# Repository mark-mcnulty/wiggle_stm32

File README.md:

# STM32_MOD_2

Firmware for a small STM32F1-based audio board: either a LUT-driven oscillator into the onboard DAC, or a short effects chain on whatever comes in on the ADC. The Cube/HAL setup is real; mixer, filter, ADSR, and sampler are mostly placeholders for now (see [Code layout](#code-layout)).

**MCU:** STM32F103RCT6  
**IDE:** STM32CubeIDE (GCC).

## Requirements

- [STM32CubeIDE](https://www.st.com/en/development-tools/stm32cubeide.html) (or IAR + pack for F1)
- ST firmware package **STM32Cube FW_F1 V1.8.6** (matches [`STM32_MOD_2.ioc`](STM32_MOD_2.ioc))

## Build and flash

1. Open [`STM32_MOD_2.ioc`](STM32_MOD_2.ioc) or import the project from this repo in CubeIDE.
2. Build the **Debug** configuration (output under `Debug/`).
3. Flash/debug with your ST-Link (or whatever probe you use in the launch config).

Regenerating code from the `.ioc` is fine; user sections in `main.c` and friends are preserved by Cube’s `USER CODE` blocks.

## Audio modes

Flip these in [`Core/Src/main.c`](Core/Src/main.c) before you build:

- `ACTIVE_AUDIO_MODE` — `SYNTH` or `EFFECTS` (passed into `init_stm32()`).
- `ACTIVE_EFFECT_MODE` — `EFFECT_BYPASS`, `EFFECT_MOVING_AVG`, or `EFFECT_BIT_CRUSHER` ([`Core/Inc/effects.h`](Core/Inc/effects.h)).
- `ACTIVE_MOVING_AVG_TAPS` — tap count for the moving average (capped in [`effects.c`](Core/Src/effects.c)).

**SYNTH:** TIM8 triggers DAC channel 2 via DMA. Half- and full-transfer callbacks call `render_audio_block()`, which fills the DAC buffer from the oscillator ([`Core/Src/stm32_synth.c`](Core/Src/stm32_synth.c), [`Core/Src/oscillator.c`](Core/Src/oscillator.c)). Waveforms are sine, square, triangle, saw, or noise ([`Core/Inc/oscillator.h`](Core/Inc/oscillator.h)). Right now the main loop runs `marry_had_a_little_lamb()` as a demo when in this mode; other tests (UART, frequency sweep, seven-seg) are commented out in the same file.

**EFFECTS:** ADC1 is also triggered off TIM8 TRGO, with DMA into `audio_buffer_adc`. ADC callbacks copy each half into `audio_buffer_sig_path`. DAC callbacks wait until the matching `adc_half_ready[]` flag is set, then run `effects_process_sample()` so output stays aligned with fresh input. Underrun/overrun counters on `struct synth` are there for debugging.

**Sample rate:** System clock is 24 MHz (HSI + PLL in `SystemClock_Config`). TIM8 is set in the IOC to prescaler 3 and period 124, which works out to about **48 kHz** for the DAC/ADC trigger rate. Audio buffers are **256** samples (`AUDIO_BUFFER_SIZE` in [`Core/Inc/stm32_synth.h`](Core/Inc/stm32_synth.h)).

## Front-panel I/O

Pin names live in [`Core/Inc/main.h`](Core/Inc/main.h): two buttons, a pot, an LED, SPI1 to a shift-register style display, plus digit select lines for a **two-digit seven-segment** display. [`Core/Src/seven_seg.c`](Core/Src/seven_seg.c) is refreshed from `HAL_TIM_PeriodElapsedCallback()` on TIM2 in `main.c`.

## Code layout

| Area | Files |
|------|--------|
| Entry, Cube init, DAC/ADC callbacks | [`Core/Src/main.c`](Core/Src/main.c) |
| Mode init, `render_audio_block`, ADC staging | [`Core/Src/stm32_synth.c`](Core/Src/stm32_synth.c), [`Core/Inc/stm32_synth.h`](Core/Inc/stm32_synth.h) |
| Oscillator / LUT | [`Core/Src/oscillator.c`](Core/Src/oscillator.c), [`Core/Inc/oscillator.h`](Core/Inc/oscillator.h) |
| Effects | [`Core/Src/effects.c`](Core/Src/effects.c), [`Core/Inc/effects.h`](Core/Inc/effects.h) |
| Note frequencies | [`Core/Inc/notes.h`](Core/Inc/notes.h) |
| Seven-segment + SPI | [`Core/Src/seven_seg.c`](Core/Src/seven_seg.c), [`Core/Inc/seven_seg.h`](Core/Inc/seven_seg.h) |

**Not wired into the synth audio path yet:** `struct synth` already holds mixer, filter, and ADSR, and [`mixer.c`](Core/Src/mixer.c) implements a simple average of sources, but `render_audio_block()` only comments those stages—no calls. [`filter.c`](Core/Src/filter.c), [`adsr.c`](Core/Src/adsr.c), and [`sampler.c`](Core/Src/sampler.c) are empty or stub implementations.

## Hardware and diagrams

KiCad lives under [`Hardware/`](Hardware/). The project file is [`Hardware/STM_Module.kicad_pro`](Hardware/STM_Module.kicad_pro); schematics include e.g. [`Hardware/STM32.kicad_sch`](Hardware/STM32.kicad_sch) and [`Hardware/power.kicad_sch`](Hardware/power.kicad_sch).

Block diagrams in the repo root: [`signal_path_diagram.drawio`](signal_path_diagram.drawio), [`stm32_structure.drawio`](stm32_structure.drawio).

## License

ST’s HAL/CMSIS drop in with their usual `LICENSE.txt` under `Drivers/`—nothing special added here.

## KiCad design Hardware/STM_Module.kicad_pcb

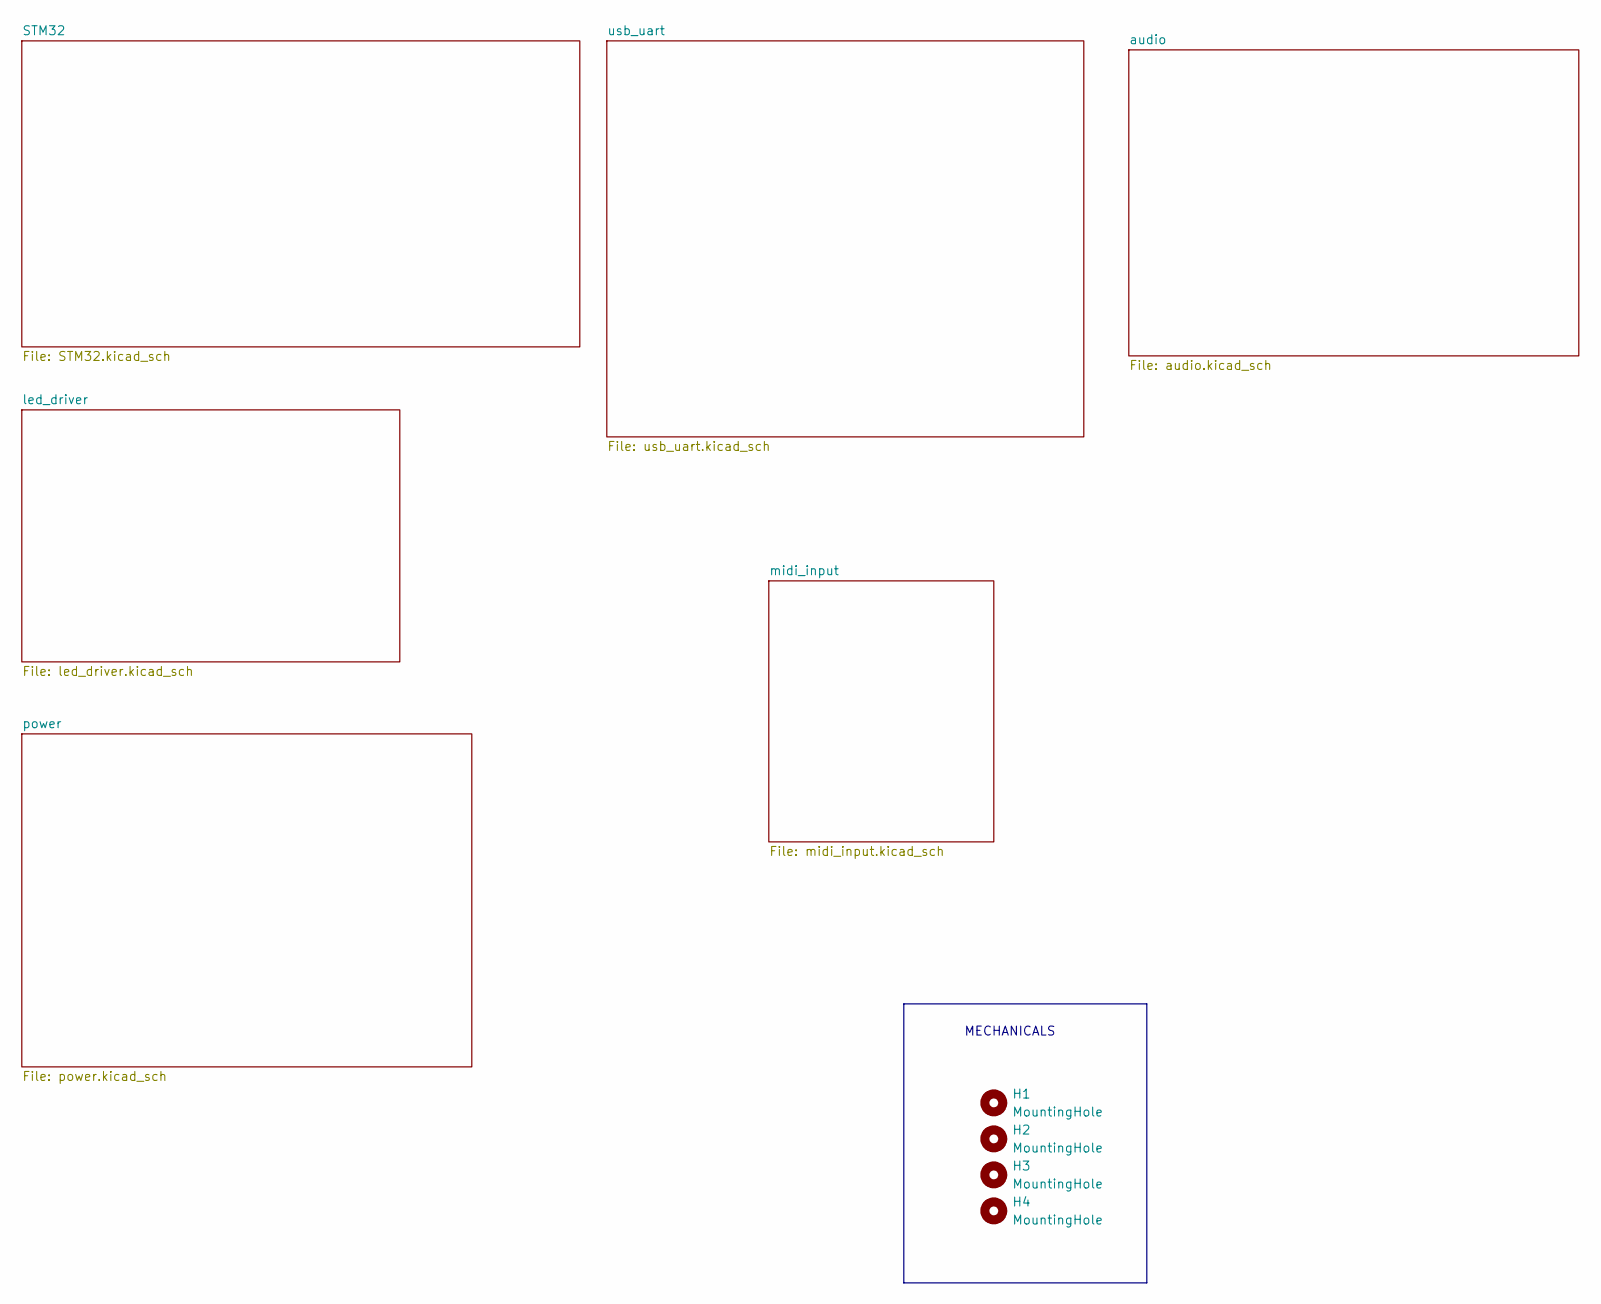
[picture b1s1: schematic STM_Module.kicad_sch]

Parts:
H1, H2, H3, H4: MountingHole; MountingHole_2.2mm_M2

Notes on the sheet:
MECHANICALS

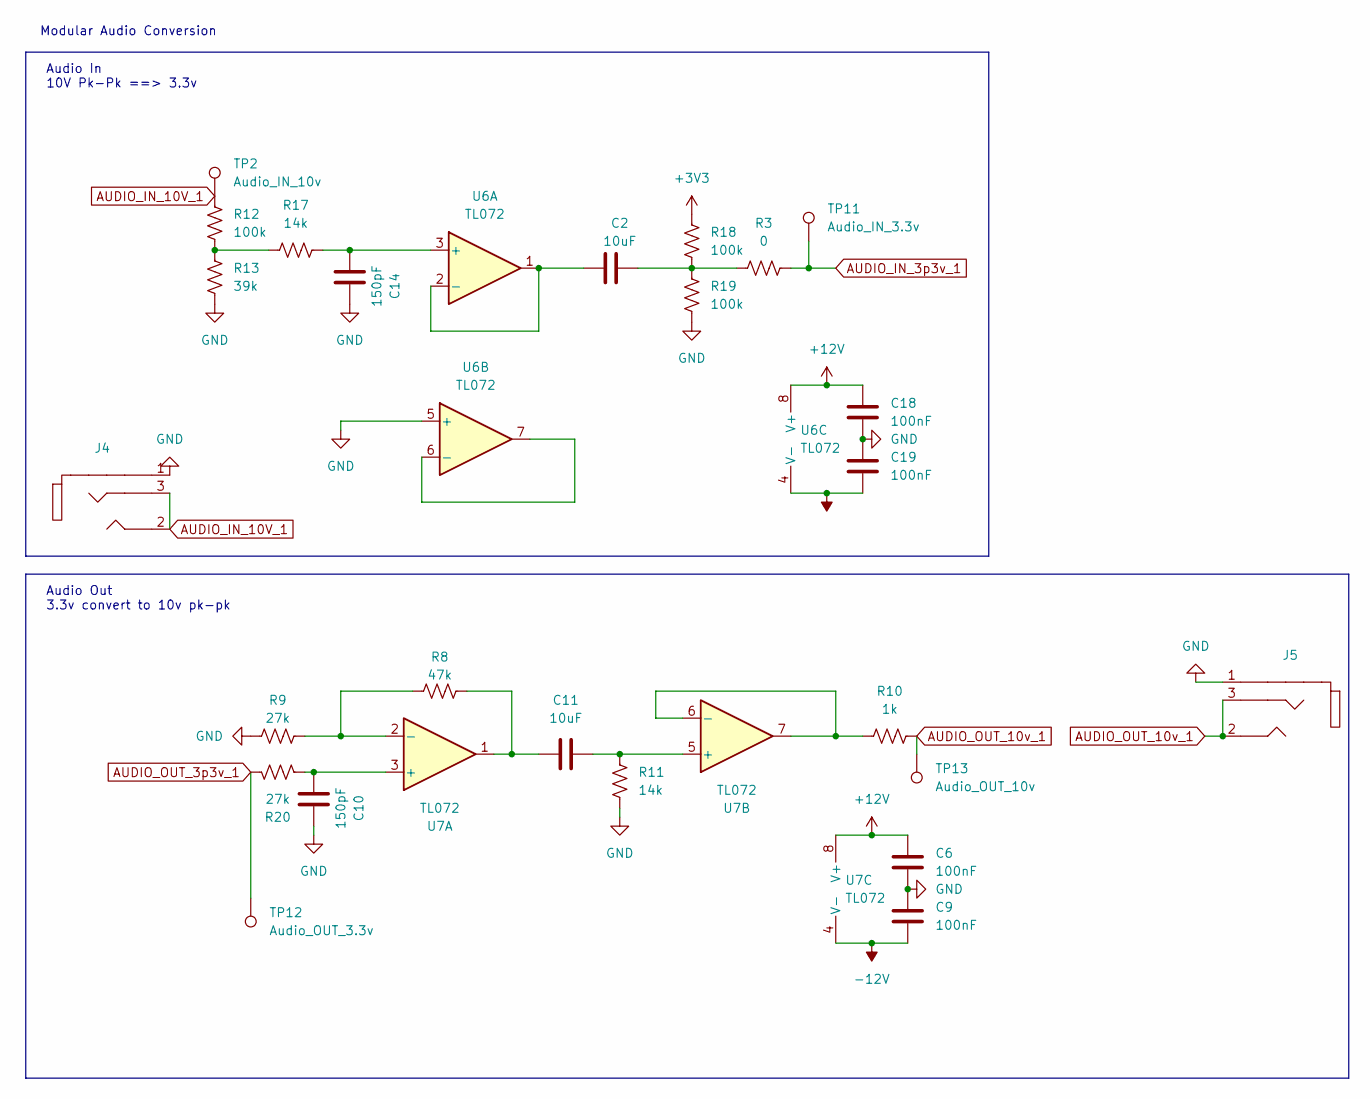
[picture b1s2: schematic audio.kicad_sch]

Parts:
C2, C11: 10uF; C_1206_3216Metric
C6, C9, C18, C19: 100nF; C_1206_3216Metric
C10, C14: 150pF; C_1206_3216Metric
J4, J5: aux
R3: 0; R_1206_3216Metric
R8: 47k; R_1206_3216Metric
R9, R20: 27k; R_1206_3216Metric
R10: 1k; R_1206_3216Metric
R11, R17: 14k; R_1206_3216Metric
R12, R18, R19: 100k; R_1206_3216Metric
R13: 39k; R_1206_3216Metric
TP2: Audio_IN_10v; PinHeader_1x01_P2.54mm_Vertical
TP11: Audio_IN_3.3v; PinHeader_1x01_P2.54mm_Vertical
TP12: Audio_OUT_3.3v; PinHeader_1x01_P2.54mm_Vertical
TP13: Audio_OUT_10v; PinHeader_1x01_P2.54mm_Vertical
U6, U7: TL072; TL072_SOIC-8

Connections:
+3V3: R18.1; also elsewhere on the board
+12V: C6.2, C18.2, U6.8 (V+), U7.8 (V+); also elsewhere on the board
-12V: C9.1, C19.1, U6.4 (V-), U7.4 (V-); also elsewhere on the board
AUDIO_IN_3p3v_1: R3.2, TP11.1; also elsewhere on the board
AUDIO_IN_10V_1: J4.2, J4.3, R12.1, TP2.1
AUDIO_OUT_3p3v_1: R20.1, TP12.1; also elsewhere on the board
AUDIO_OUT_10v_1: J5.2, J5.3, R10.2, TP13.1
GND: C6.1, C9.2, C10.1, C14.1, C18.1, C19.2, J4.1, J5.1, R9.1, R11.1, R13.2, R19.2, U6.5 (+); also elsewhere on the board
unnamed: C2.1, R3.1, R18.2, R19.1
unnamed: C11.2, R8.2, U7.1
unnamed: R12.2, R13.1, R17.1
unnamed: C14.2, R17.2, U6.3 (+)
unnamed: C2.2, U6.1, U6.2 (-)
unnamed: U6.6 (-), U6.7
unnamed: C10.2, R20.2, U7.3 (+)
unnamed: R8.1, R9.2, U7.2 (-)
unnamed: C11.1, R11.2, U7.5 (+)
unnamed: R10.1, U7.6 (-), U7.7

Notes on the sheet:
Audio Out 3.3v convert to 10v pk-pk
Audio In 10V Pk-Pk ==> 3.3v
Modular Audio Conversion

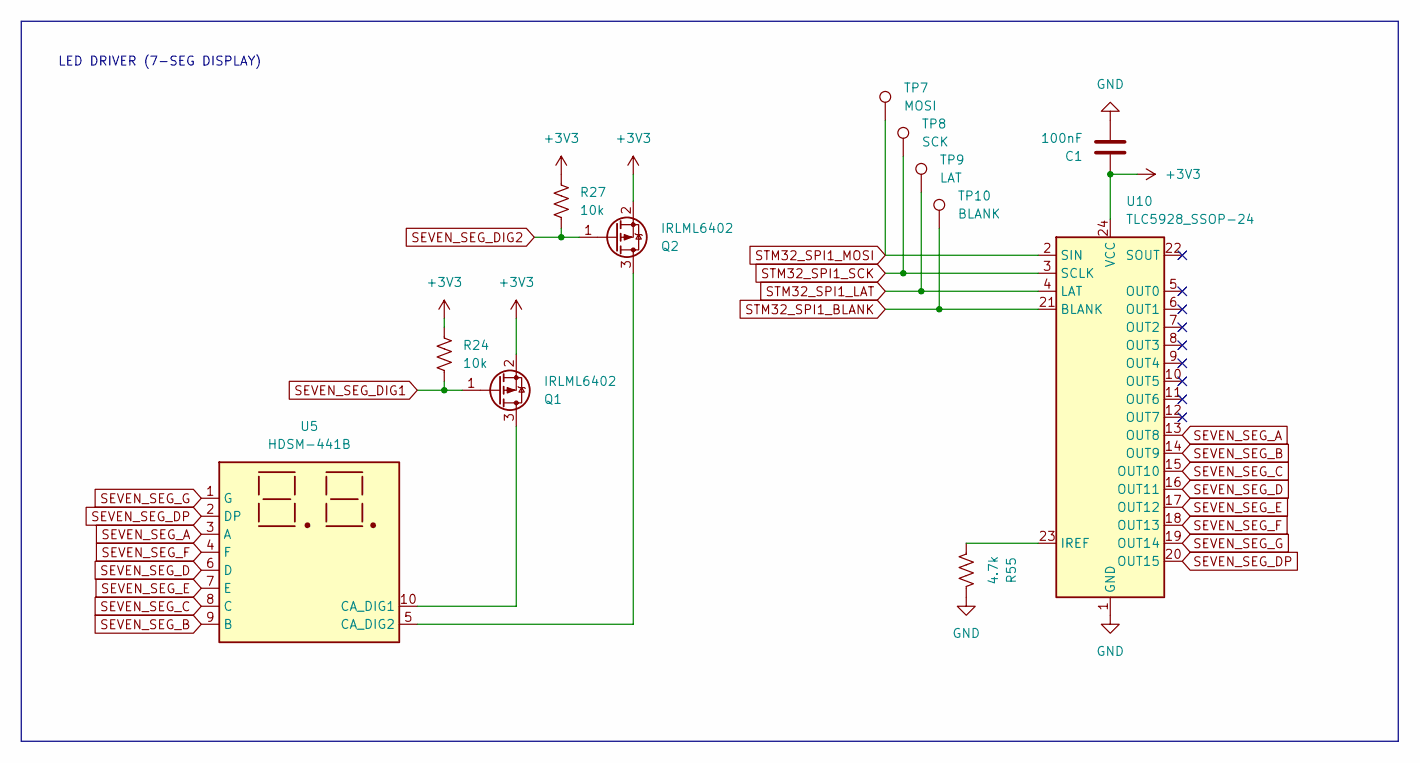
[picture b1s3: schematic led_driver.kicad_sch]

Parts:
C1: 100nF; C_1206_3216Metric
Q1, Q2: IRLML6402; SOT-23
R24, R27: 10k; R_1206_3216Metric
R55: 4.7k; R_1206_3216Metric
TP7: MOSI; PinHeader_1x01_P2.54mm_Vertical
TP8: SCK; PinHeader_1x01_P2.54mm_Vertical
TP9: LAT; PinHeader_1x01_P2.54mm_Vertical
TP10: BLANK; PinHeader_1x01_P2.54mm_Vertical
U5: HDSM-441B; 2x7 SEG LCSC C193139
U10: TLC5928_SSOP-24

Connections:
+3V3: C1.1, Q1.2 (S), Q2.2 (S), R24.1, R27.1, U10.24 (VCC); also elsewhere on the board
GND: C1.2, R55.1, U10.1 (GND); also elsewhere on the board
unnamed: Q1.3 (D), U5.10 (CA_DIG1)
unnamed: Q2.3 (D), U5.5 (CA_DIG2)
unnamed: R55.2, U10.23 (IREF)
SEVEN_SEG_A: U5.3 (A), U10.13 (OUT8)
SEVEN_SEG_B: U5.9 (B), U10.14 (OUT9)
SEVEN_SEG_C: U5.8 (C), U10.15 (OUT10)
SEVEN_SEG_D: U5.6 (D), U10.16 (OUT11)
SEVEN_SEG_DIG1: Q1.1 (G), R24.2; also elsewhere on the board
SEVEN_SEG_DIG2: Q2.1 (G), R27.2; also elsewhere on the board
SEVEN_SEG_DP: U5.2 (DP), U10.20 (OUT15)
SEVEN_SEG_E: U5.7 (E), U10.17 (OUT12)
SEVEN_SEG_F: U5.4 (F), U10.18 (OUT13)
SEVEN_SEG_G: U5.1 (G), U10.19 (OUT14)
STM32_SPI1_BLANK: TP10.1, U10.21 (BLANK); also elsewhere on the board
STM32_SPI1_LAT: TP9.1, U10.4 (LAT); also elsewhere on the board
STM32_SPI1_MOSI: TP7.1, U10.2 (SIN); also elsewhere on the board
STM32_SPI1_SCK: TP8.1, U10.3 (SCLK); also elsewhere on the board

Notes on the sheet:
LED DRIVER (7-SEG DISPLAY)

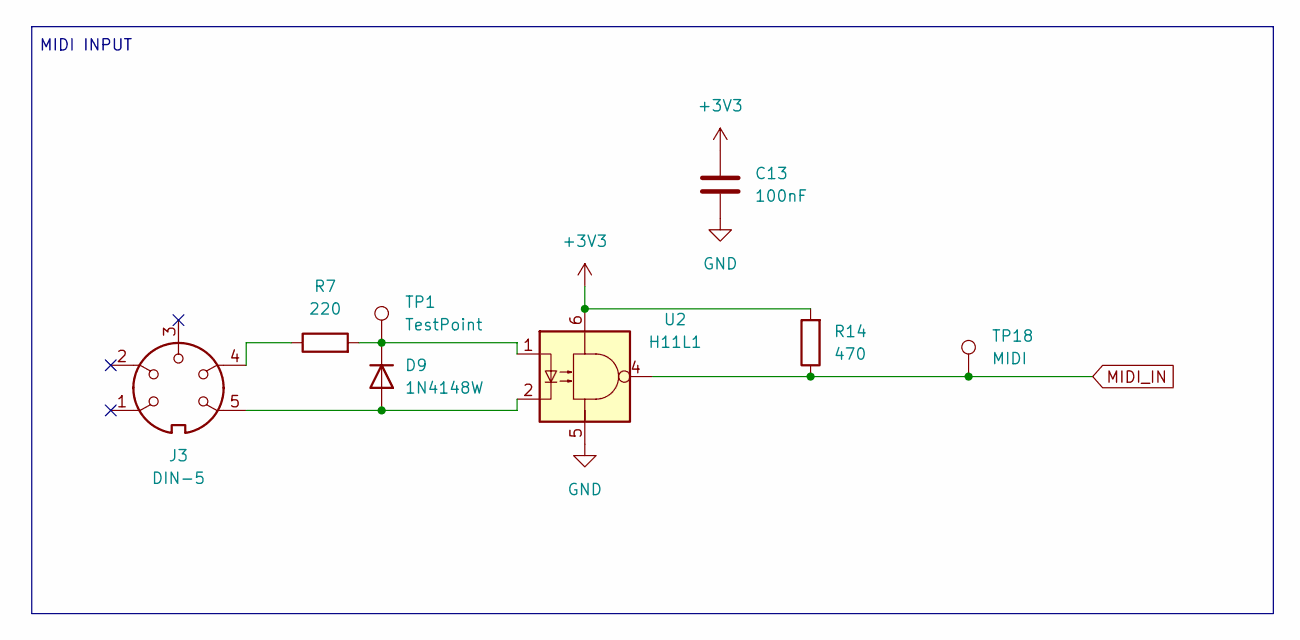
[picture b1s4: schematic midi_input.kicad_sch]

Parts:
C13: 100nF; C_1206_3216Metric
D9: 1N4148W; D_SOD-123
J3: DIN-5; Din5
R7: 220; R_1206_3216Metric
R14: 470; R_1206_3216Metric
TP1: TestPoint; PinHeader_1x01_P2.54mm_Vertical
TP18: MIDI; PinHeader_1x01_P2.54mm_Vertical
U2: H11L1; H11L1_SMD

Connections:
+3V3: C13.1, R14.2, U2.6; also elsewhere on the board
GND: C13.2, U2.5; also elsewhere on the board
MIDI_IN: R14.1, TP18.1, U2.4; also elsewhere on the board
unnamed: D9.2 (A), J3.5, U2.2
unnamed: D9.1 (K), R7.2, TP1.1, U2.1
unnamed: J3.4, R7.1

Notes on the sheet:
MIDI INPUT

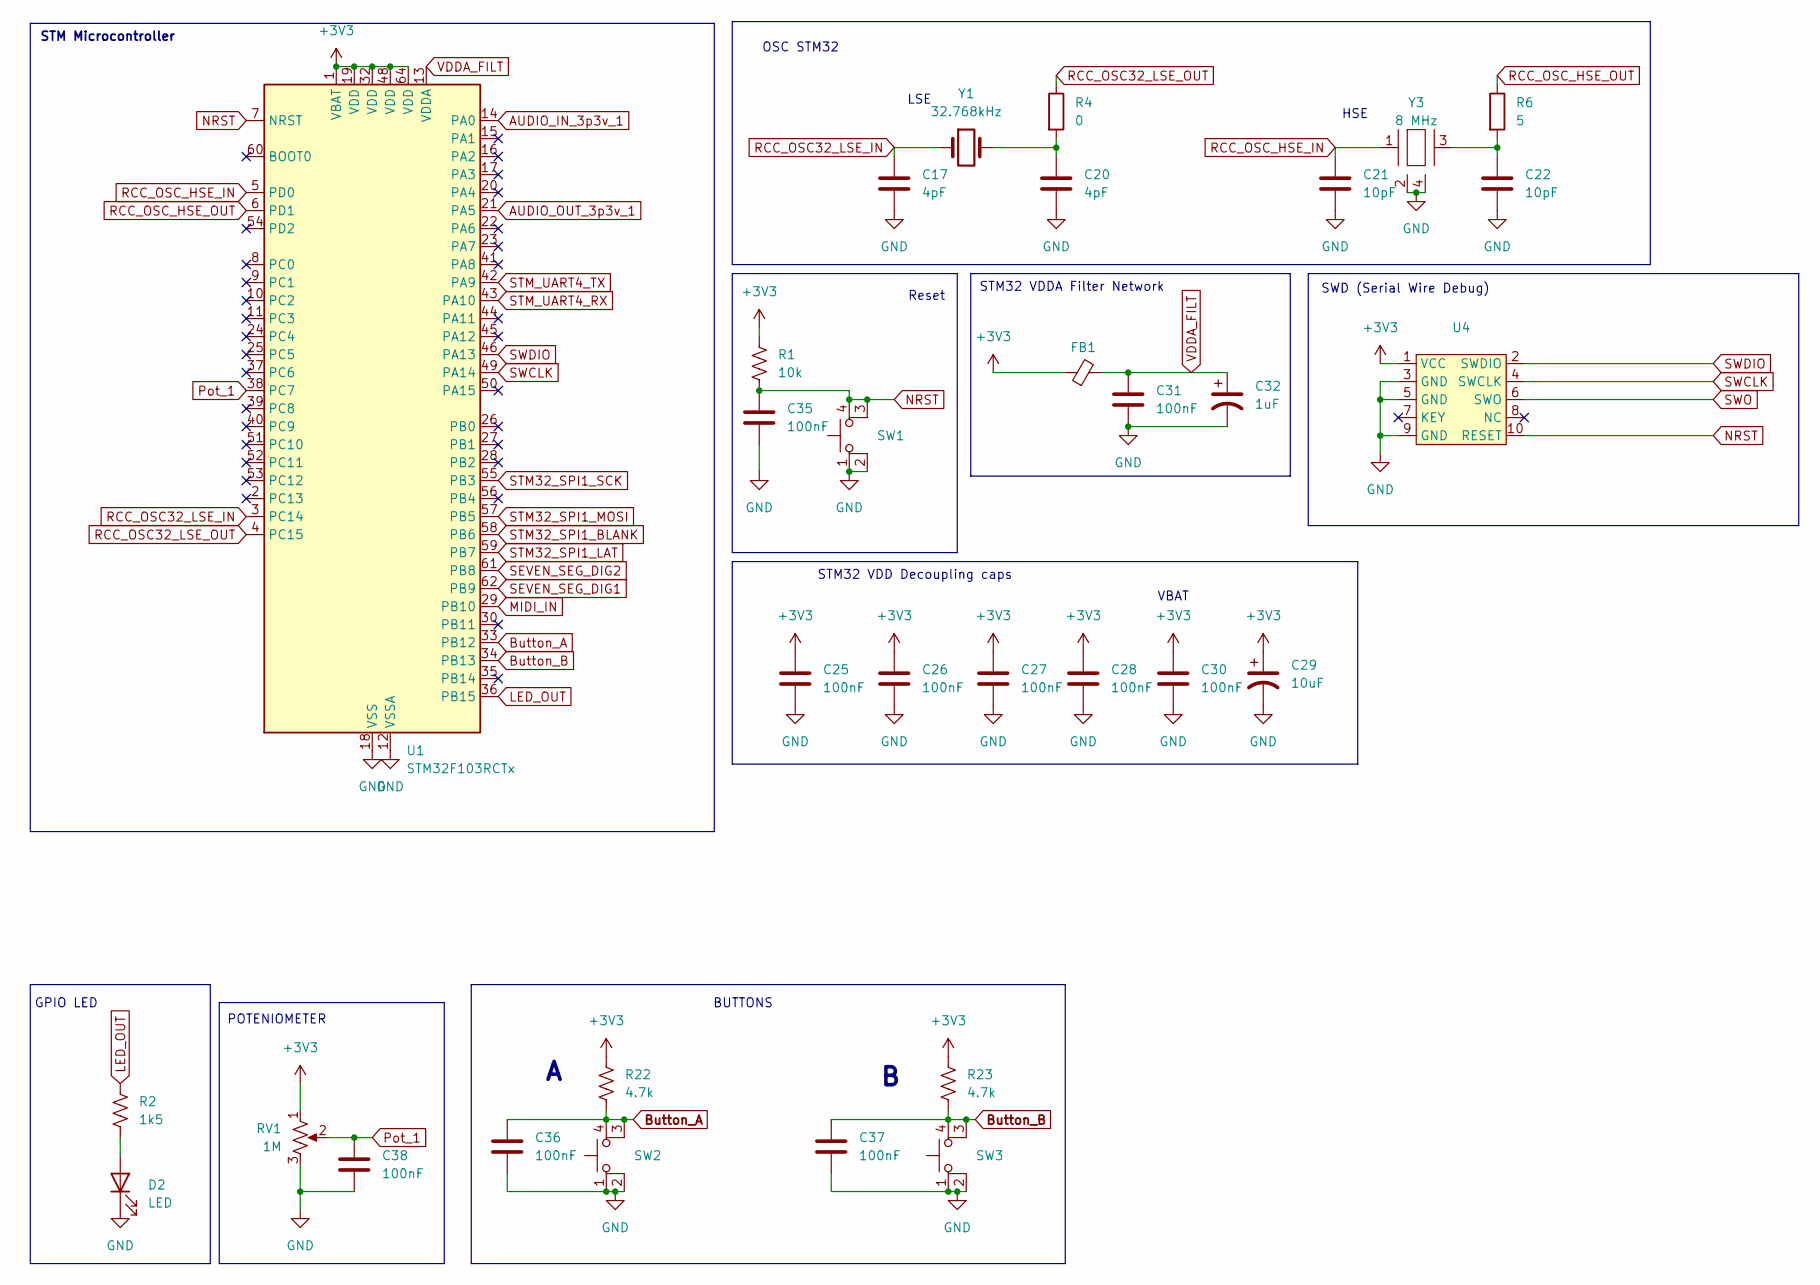
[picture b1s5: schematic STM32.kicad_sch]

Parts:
C17, C20: 4pF; C_0603_1608Metric
C21, C22: 10pF; C_0603_1608Metric
C25, C26, C27, C28, C30, C31, C35, C36, C37, C38: 100nF; C_1206_3216Metric
C29: 10uF; CP_Elec_4x5.4
C32: 1uF; CP_Elec_4x5.4
D2: LED; LED_1206_3216Metric
FB1: FerriteBead_Small; R_1206_3216Metric
R1: 10k; R_1206_3216Metric
R2: 1k5; R_1206_3216Metric
R4: 0; R_1206_3216Metric
R6: 5; R_1206_3216Metric
R22, R23: 4.7k; R_1206_3216Metric
RV1: 1M; POT_mogaopi
SW1, SW2, SW3: SW_MEC_5E; Button PN C381039
U1: STM32F103RCTx; LQFP-64_10x10mm_P0.5mm
U4: PinHeader_2x05_P2.54mm_Vertical
Y1: 32.768kHz; Crystal_SMD_2012-2Pin_2.0x1.2mm
Y3: 8 MHz; 12MHz Surface Mount Crystal 12pF ±10ppm ±20ppm SMD3225-4P C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

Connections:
+3V3: C25.2, C26.2, C27.2, C28.2, C29.1, C30.2, FB1.1, R1.2, R22.1, R23.1, RV1.1, U1.1 (VBAT), U1.19 (VDD), U1.32 (VDD), U1.48 (VDD), U1.64 (VDD), U4.1 (VCC); also elsewhere on the board
AUDIO_IN_3p3v_1: U1.14 (PA0); also elsewhere on the board
AUDIO_OUT_3p3v_1: U1.21 (PA5); also elsewhere on the board
Button_A: C36.2, R22.2, SW2.3 (K), SW2.4 (A), U1.33 (PB12)
Button_B: C37.2, R23.2, SW3.3 (K), SW3.4 (A), U1.34 (PB13)
GND: C17.1, C20.1, C21.1, C22.1, C25.1, C26.1, C27.1, C28.1, C29.2, C30.1, C31.1, C32.2, C35.1, C36.1, C37.1, C38.1, D2.1 (K), RV1.3, SW1.1, SW1.2, SW2.1, SW2.2, SW3.1, SW3.2, U1.12 (VSSA), U1.18 (VSS), U1.31 (VSS), U1.47 (VSS), U1.63 (VSS), U4.3 (GND), U4.5 (GND), U4.9 (GND), Y3.2, Y3.4; also elsewhere on the board
LED_OUT: R2.1, U1.36 (PB15)
MIDI_IN: U1.29 (PB10); also elsewhere on the board
NRST: C35.2, R1.1, SW1.3 (K), SW1.4 (A), U1.7 (NRST), U4.10 (RESET)
unnamed: C20.2, R4.2, Y1.2
unnamed: C22.2, R6.2, Y3.3
unnamed: D2.2 (A), R2.2
Pot_1: C38.2, RV1.2, U1.38 (PC7)
RCC_OSC32_LSE_IN: C17.2, U1.3 (PC14), Y1.1
RCC_OSC32_LSE_OUT: R4.1, U1.4 (PC15)
RCC_OSC_HSE_IN: C21.2, U1.5 (PD0), Y3.1
RCC_OSC_HSE_OUT: R6.1, U1.6 (PD1)
SEVEN_SEG_DIG1: U1.62 (PB9); also elsewhere on the board
SEVEN_SEG_DIG2: U1.61 (PB8); also elsewhere on the board
STM32_SPI1_BLANK: U1.58 (PB6); also elsewhere on the board
STM32_SPI1_LAT: U1.59 (PB7); also elsewhere on the board
STM32_SPI1_MOSI: U1.57 (PB5); also elsewhere on the board
STM32_SPI1_SCK: U1.55 (PB3); also elsewhere on the board
STM_UART4_RX: U1.43 (PA10); also elsewhere on the board
STM_UART4_TX: U1.42 (PA9); also elsewhere on the board
SWCLK: U1.49 (PA14), U4.4 (SWCLK)
SWDIO: U1.46 (PA13), U4.2 (SWDIO)
SWO: U4.6 (SWO)
VDDA_FILT: C31.2, C32.1, FB1.2, U1.13 (VDDA)

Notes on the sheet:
STM Microcontroller
LSE
VBAT
GPIO LED
STM32 VDDA Filter Network
OSC STM32
BUTTONS
STM32 VDD Decoupling caps
Reset
POTENIOMETER
SWD (Serial Wire Debug)
HSE

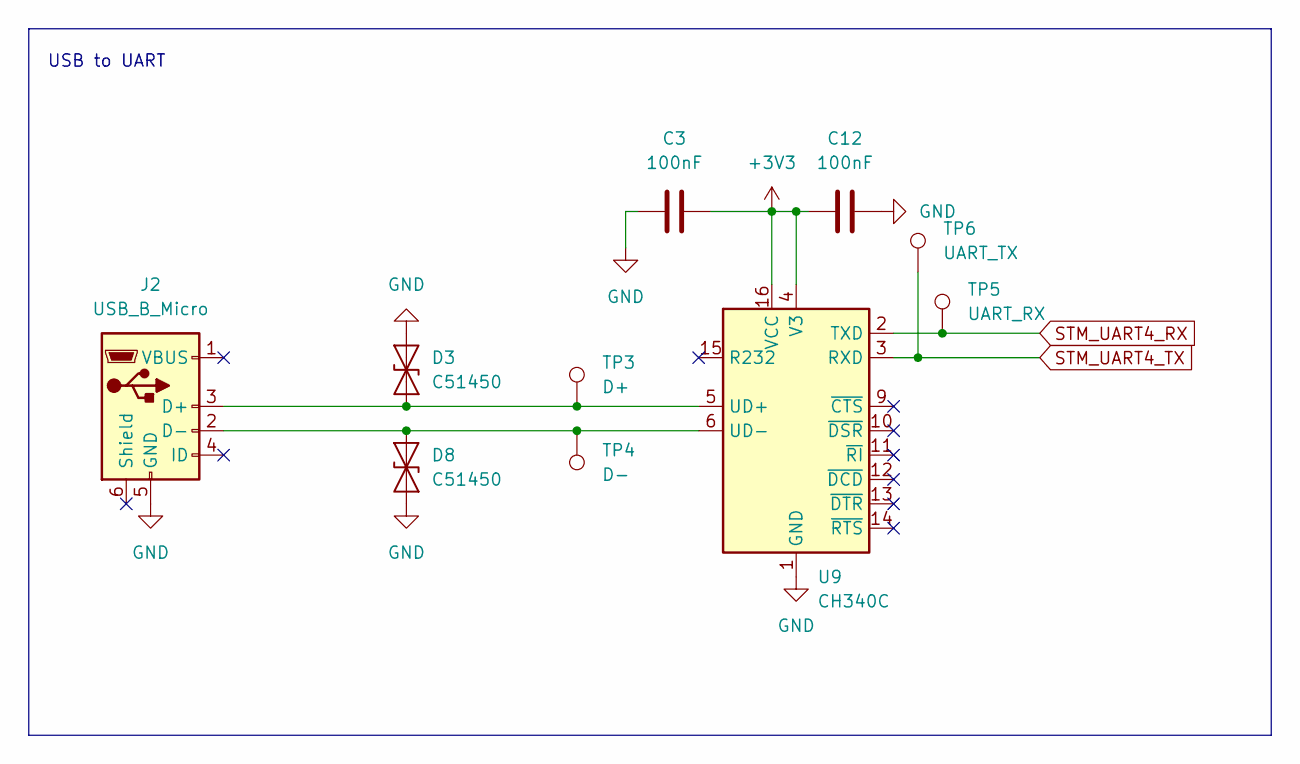
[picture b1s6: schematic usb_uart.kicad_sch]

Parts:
C3, C12: 100nF; C_1206_3216Metric
D3, D8: C51450; D_SOD-323
J2: USB_B_Micro; USB Mini-B MFN, U-M-M5DD-W-4
TP3: D+; PinHeader_1x01_P2.54mm_Vertical
TP4: D-; PinHeader_1x01_P2.54mm_Vertical
TP5: UART_RX; PinHeader_1x01_P2.54mm_Vertical
TP6: UART_TX; PinHeader_1x01_P2.54mm_Vertical
U9: CH340C; SOIC-16_3.9x9.9mm_P1.27mm

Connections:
+3V3: C3.2, C12.1, U9.4 (V3), U9.16 (VCC); also elsewhere on the board
GND: C3.1, C12.2, D3.2 (A2), D8.2 (A2), J2.5 (GND), U9.1 (GND); also elsewhere on the board
unnamed: D3.1 (A1), J2.3 (D+), TP3.1, U9.5 (UD+)
unnamed: D8.1 (A1), J2.2 (D-), TP4.1, U9.6 (UD-)
STM_UART4_RX: TP5.1, U9.2 (TXD); also elsewhere on the board
STM_UART4_TX: TP6.1, U9.3 (RXD); also elsewhere on the board

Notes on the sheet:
USB to UART

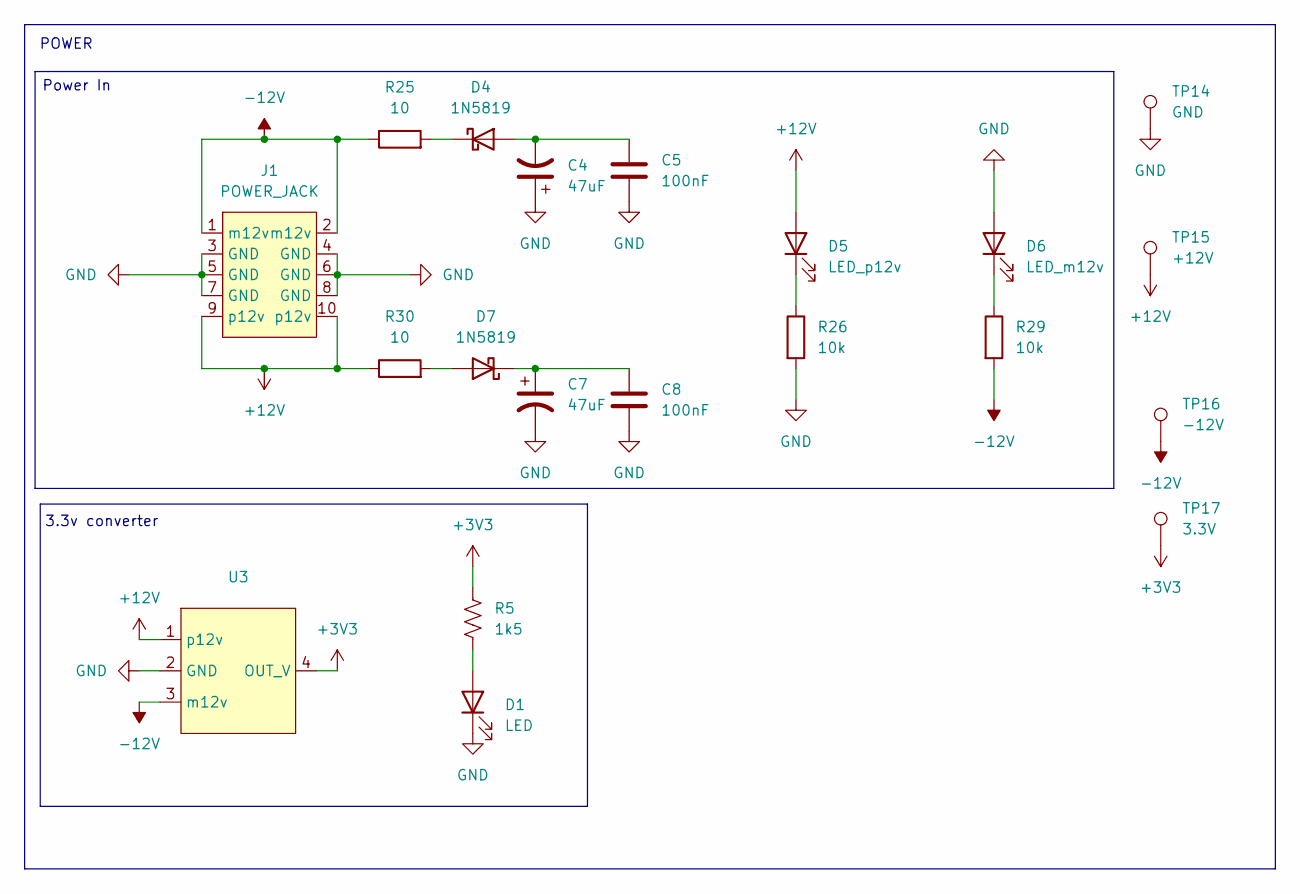
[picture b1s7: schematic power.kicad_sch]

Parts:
C4, C7: 47uF; CP_Elec_6.3x5.4_Nichicon
C5, C8: 100nF; C_1206_3216Metric
D1: LED; LED_1206_3216Metric
D4, D7: 1N5819; D_SOD-123
D5: LED_p12v; LED_1206_3216Metric_Pad1.42x1.75mm_HandSolder
D6: LED_m12v; LED_1206_3216Metric_Pad1.42x1.75mm_HandSolder
J1: POWER_JACK; euro_rack_power
R5: 1k5; R_1206_3216Metric
R25, R30: 10; R_1206_3216Metric
R26, R29: 10k; R_1206_3216Metric
TP14: GND; PinHeader_1x01_P2.54mm_Vertical
TP15: +12V; PinHeader_1x01_P2.54mm_Vertical
TP16: -12V; PinHeader_1x01_P2.54mm_Vertical
TP17: 3.3V; PinHeader_1x01_P2.54mm_Vertical
U3: pwr_mez_3in_1out

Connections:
+3V3: R5.1, TP17.1, U3.4 (OUT_V); also elsewhere on the board
+12V: D5.2 (A), J1.9 (p12v), J1.10 (p12v), R30.1, TP15.1, U3.1 (p12v); also elsewhere on the board
-12V: J1.1 (m12v), J1.2 (m12v), R25.1, R29.2, TP16.1, U3.3 (m12v); also elsewhere on the board
GND: C4.1, C5.2, C7.2, C8.2, D1.1 (K), D6.2 (A), J1.3 (GND), J1.4 (GND), J1.5 (GND), J1.6 (GND), J1.7 (GND), J1.8 (GND), R26.2, TP14.1, U3.2 (GND); also elsewhere on the board
unnamed: D1.2 (A), R5.2
unnamed: C4.2, C5.1, D4.2 (A)
unnamed: D4.1 (K), R25.2
unnamed: D5.1 (K), R26.1
unnamed: D6.1 (K), R29.1
unnamed: D7.2 (A), R30.2
unnamed: C7.1, C8.1, D7.1 (K)

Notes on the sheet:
Power In
3.3v converter
POWER

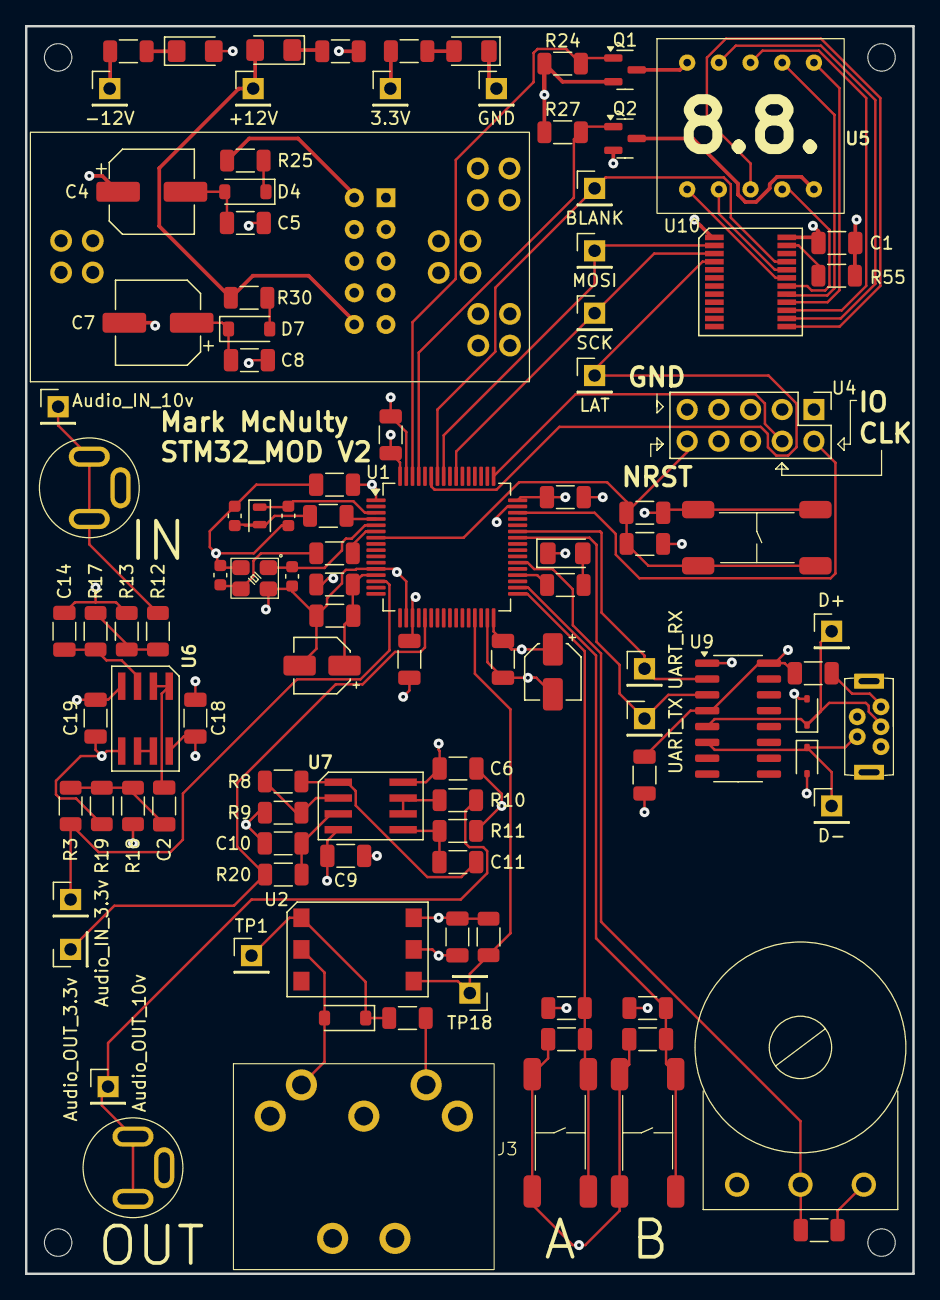
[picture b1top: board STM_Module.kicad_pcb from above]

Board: 4 copper layers, 71.1 x 100.0 mm, 113 parts (1 on the bottom side), 65 nets.

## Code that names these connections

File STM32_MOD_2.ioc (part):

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Mcu.Name=STM32F103R(C-D-E)Tx
Mcu.Package=LQFP64
Mcu.UserName=STM32F103RCTx
PA0-WKUP.Signal=ADCx_IN0
PA10.Mode=Asynchronous
PA10.Signal=USART1_RX
PA13.Mode=Serial_Wire
PA13.Signal=SYS_JTMS-SWDIO
PA14.Mode=Serial_Wire
PA14.Signal=SYS_JTCK-SWCLK
PA5.Signal=COMP_DAC2_group
PA9.Mode=Asynchronous
PA9.Signal=USART1_TX
PB10.Signal=GPIO_Input
PB12.GPIOParameters=GPIO_Label
PB12.GPIO_Label=Button_A
PB12.Signal=GPIO_Input
PB13.GPIOParameters=GPIO_Label
PB13.GPIO_Label=Button_B
PB13.Signal=GPIO_Input
PB15.GPIOParameters=PinState,GPIO_PuPd,GPIO_Label,GPIO_ModeDefaultOutputPP
PB15.GPIO_Label=LED_OUT
PB15.GPIO_ModeDefaultOutputPP=GPIO_MODE_OUTPUT_PP
PB15.GPIO_PuPd=GPIO_PULLDOWN
PB15.PinState=GPIO_PIN_RESET
PB15.Signal=GPIO_Output
PB3.Mode=TX_Only_Simplex_Unidirect_Master
PB3.Signal=SPI1_SCK
PB5.Mode=TX_Only_Simplex_Unidirect_Master
PB5.Signal=SPI1_MOSI
PB6.GPIOParameters=GPIO_Label
PB6.GPIO_Label=SPI_BLANK
PB6.Signal=GPIO_Output
PB7.GPIOParameters=GPIO_Speed,PinState,GPIO_Label
PB7.GPIO_Label=SPI_LAT
PB7.GPIO_Speed=GPIO_SPEED_FREQ_HIGH
PB7.PinState=GPIO_PIN_SET
PB7.Signal=GPIO_Output
PB8.GPIOParameters=GPIO_Speed,PinState,GPIO_Label
PB8.GPIO_Label=SEVEN_SEG_DIG_0
PB8.GPIO_Speed=GPIO_SPEED_FREQ_MEDIUM
PB8.PinState=GPIO_PIN_SET
PB8.Signal=GPIO_Output
PB9.GPIOParameters=GPIO_Speed,PinState,GPIO_Label
PB9.GPIO_Label=SEVEN_SEG_DIG_1
PB9.GPIO_Speed=GPIO_SPEED_FREQ_MEDIUM
PB9.PinState=GPIO_PIN_SET
PB9.Signal=GPIO_Output
PC14-OSC32_IN.Mode=LSE-External-Oscillator
PC14-OSC32_IN.Signal=RCC_OSC32_IN
PC15-OSC32_OUT.Mode=LSE-External-Oscillator
PC15-OSC32_OUT.Signal=RCC_OSC32_OUT
PC7.GPIOParameters=GPIO_Label
PC7.GPIO_Label=Pot_1
PC7.Signal=GPIO_Input
PD0-OSC_IN.Mode=HSE-External-Oscillator
PD0-OSC_IN.Signal=RCC_OSC_IN
PD1-OSC_OUT.Mode=HSE-External-Oscillator
PD1-OSC_OUT.Signal=RCC_OSC_OUT
RCC.HSEDivPLL=RCC_HSE_PREDIV_DIV2
RCC.SYSCLKFreq_VALUE=24000000
RCC.SYSCLKSource=RCC_SYSCLKSOURCE_PLLCLK
board=custom

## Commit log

2025-09-28 start
2025-09-28 added readme
2025-09-28 added note class
2025-10-02 setting up files for tone interrupt... and adjust seven seg update rate
2025-10-02 changed the class name
2025-10-02 construction of the oscillator class
2025-11-11 added in oscillator function
2025-11-11 forgot to make a branch
2025-11-14 code cleanup and inital stuff for DMA
2025-11-14 code cleanup
2025-11-16 the DMA is working in the current config, added more code structure
2025-11-16 simple changes, still operational
2025-11-17 stuff
2025-11-17 added comments
2025-11-23 idk hope it doesn't break anything
2025-11-23 added a mixer function - don't know if it works
2025-11-23 i don't even know
2025-11-24 status: unsure
2025-11-24 changed synth structs names
2025-11-24 added some seven seg outputs
2025-11-24 seven segment display class clean up
2025-12-12 not sure still working
2025-12-31 the effects mode is working with a bug, it has sharp spikes when outputting the incoming wav, trying to fix with next commits
2025-12-31 working condition, still has glitches when applying negative time shifts to buffer position
2026-02-19 i don't even know what its doing rn
2026-03-06 working EFFECTS state, as long as 1to1
2026-03-06 working state, fixed glitches with n-1 EFFECTS, changed selection type for synth class
2026-03-06 EFFECTS working, implemented rudimentary effect selection
2026-03-08 UNTESTED: Implemented EFFECTS_MOVING_AVG which has an adjustable tap value for moving avg
2026-03-08 TESTED: EFFECTS_MOVING_AVG works
2026-03-08 Tested: added clean up on the effects... put it in its own class
2026-03-08 strays
2026-03-10 added bit crusher effect, not tested well
2026-03-20 Added my KiCad PCB files
2026-03-20 More detailed readme
2026-03-20 small corrections
